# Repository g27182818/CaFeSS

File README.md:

# CaFeSS

Repository of the Cacao Fermentation Sensing System (CaFeSS) project. This is an effort by the BioMicrosystems group at Universidad de los Andes and is Authored by Gabriel Mejia and Santiago Tovar.

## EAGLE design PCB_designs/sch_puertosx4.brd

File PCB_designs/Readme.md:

### PCB Deigns

These are the Eagle files needed for the electronic components of CaFeSS

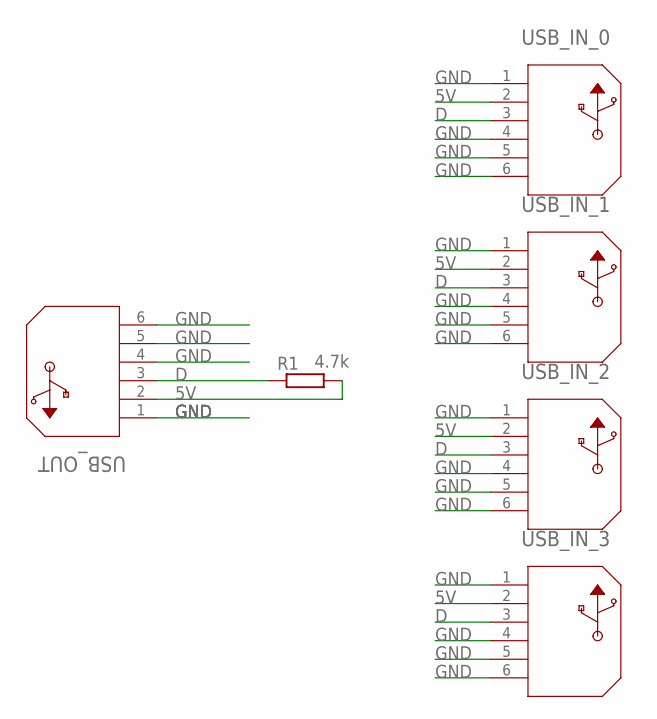
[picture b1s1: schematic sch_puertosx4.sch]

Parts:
R1: 4.7k; 0309/10
USB_IN_0, USB_IN_1, USB_IN_2, USB_IN_3: 292303-3; CONN4_292303_TEC
USB_OUT: 292303-3; CONN4_292303_TEC

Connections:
5V: R1.2, USB_IN_0.2, USB_IN_1.2, USB_IN_2.2, USB_IN_3.2, USB_OUT.2
D: R1.1, USB_IN_0.3, USB_IN_1.3, USB_IN_2.3, USB_IN_3.3, USB_OUT.3
GND: USB_IN_0.1, USB_IN_0.4, USB_IN_0.5, USB_IN_0.6, USB_IN_1.1, USB_IN_1.4, USB_IN_1.5, USB_IN_1.6, USB_IN_2.1, USB_IN_2.4, USB_IN_2.5, USB_IN_2.6, USB_IN_3.1, USB_IN_3.4, USB_IN_3.5, USB_IN_3.6, USB_OUT.1, USB_OUT.4, USB_OUT.5, USB_OUT.6

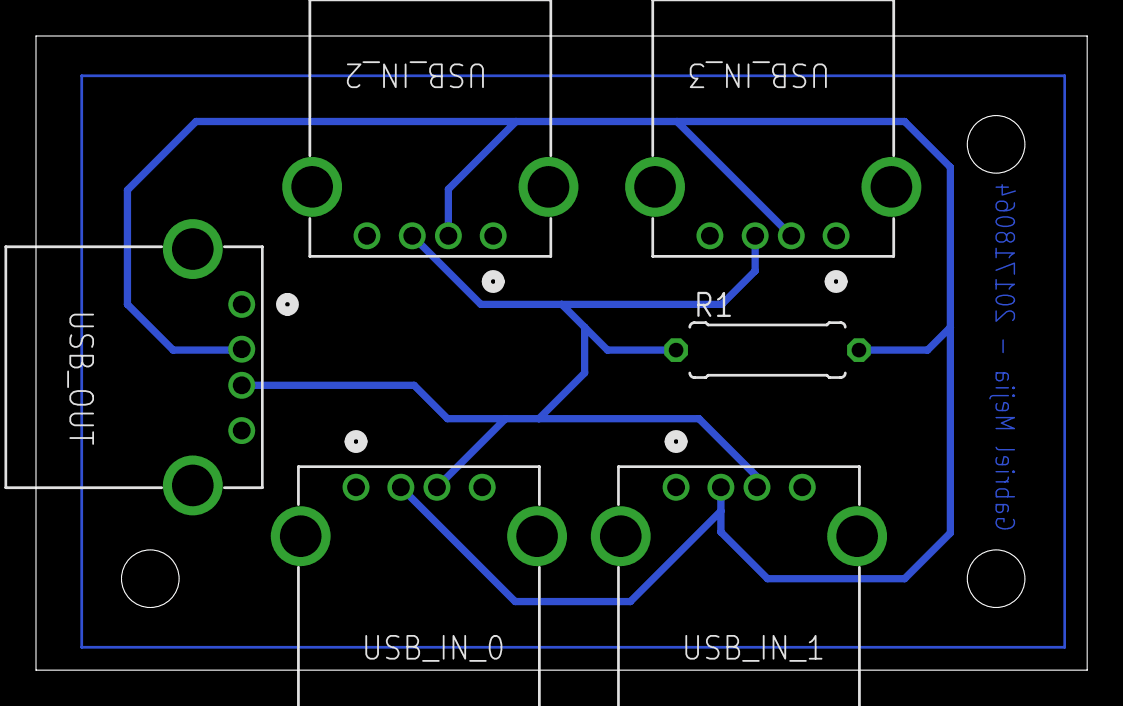
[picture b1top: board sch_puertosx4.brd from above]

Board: 2 copper layers, 58.4 x 35.2 mm, 6 parts (0 on the bottom side), 3 nets.

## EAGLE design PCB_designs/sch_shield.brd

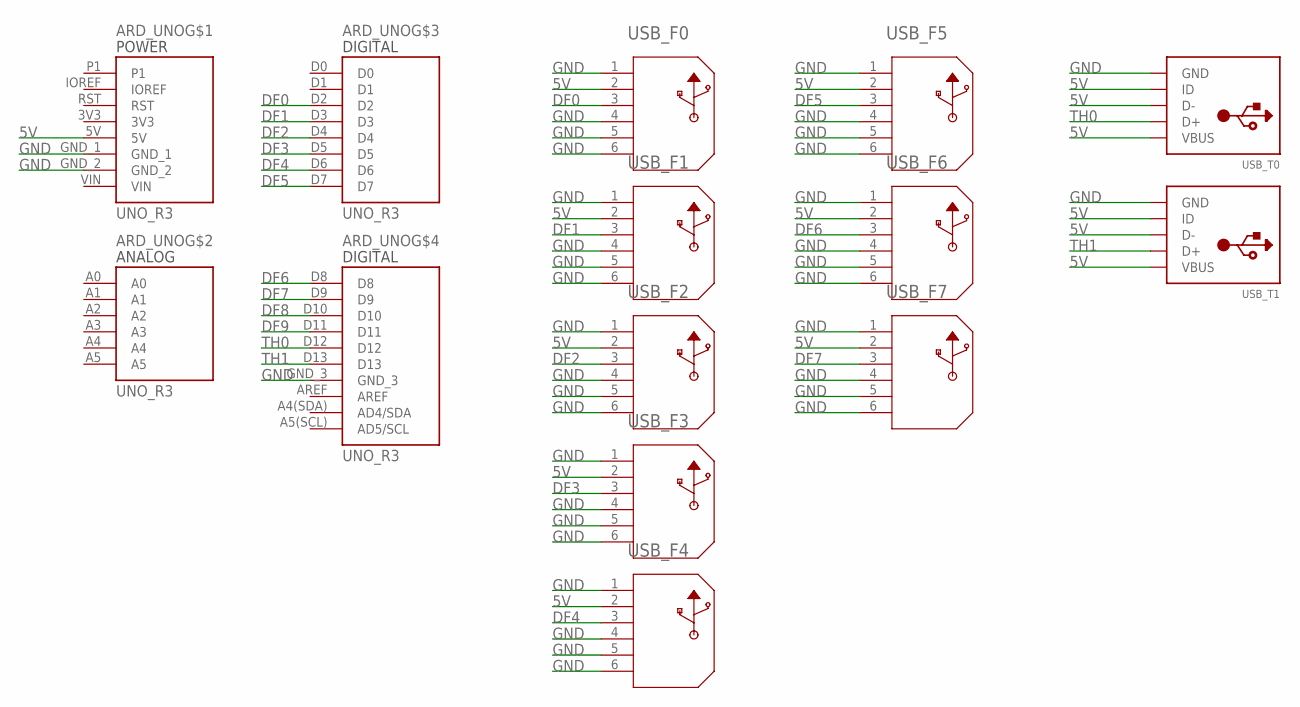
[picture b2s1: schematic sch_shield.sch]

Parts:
ARD_UNO: UNO_R3; ARDUINO_UNO_R3
USB_F0, USB_F1, USB_F2, USB_F3, USB_F4, USB_F5, USB_F6, USB_F7: 292303-3; CONN4_292303_TEC
USB_T0, USB_T1: USBTHM; USB-MINIB-THM

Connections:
3V3: ARD_UNO.3V3
5V: ARD_UNO.5V, USB_F0.2, USB_F1.2, USB_F2.2, USB_F3.2, USB_F4.2, USB_F5.2, USB_F6.2, USB_F7.2, USB_T0.D-, USB_T0.ID, USB_T0.VBUS, USB_T1.D-, USB_T1.ID, USB_T1.VBUS
DF0: ARD_UNO.D2, USB_F0.3
DF1: ARD_UNO.D3, USB_F1.3
DF2: ARD_UNO.D4, USB_F2.3
DF3: ARD_UNO.D5, USB_F3.3
DF4: ARD_UNO.D6, USB_F4.3
DF5: ARD_UNO.D7, USB_F5.3
DF6: ARD_UNO.D8, USB_F6.3
DF7: ARD_UNO.D9, USB_F7.3
DF8: ARD_UNO.D10
DF9: ARD_UNO.D11
GND: ARD_UNO.GND_1, ARD_UNO.GND_2, ARD_UNO.GND_3, USB_F0.1, USB_F0.4, USB_F0.5, USB_F0.6, USB_F1.1, USB_F1.4, USB_F1.5, USB_F1.6, USB_F2.1, USB_F2.4, USB_F2.5, USB_F2.6, USB_F3.1, USB_F3.4, USB_F3.5, USB_F3.6, USB_F4.1, USB_F4.4, USB_F4.5, USB_F4.6, USB_F5.1, USB_F5.4, USB_F5.5, USB_F5.6, USB_F6.1, USB_F6.4, USB_F6.5, USB_F6.6, USB_F7.1, USB_F7.4, USB_F7.5, USB_F7.6, USB_T0.GND, USB_T1.GND
TH0: ARD_UNO.D12, USB_T0.D+
TH1: ARD_UNO.D13, USB_T1.D+
VIN: ARD_UNO.VIN

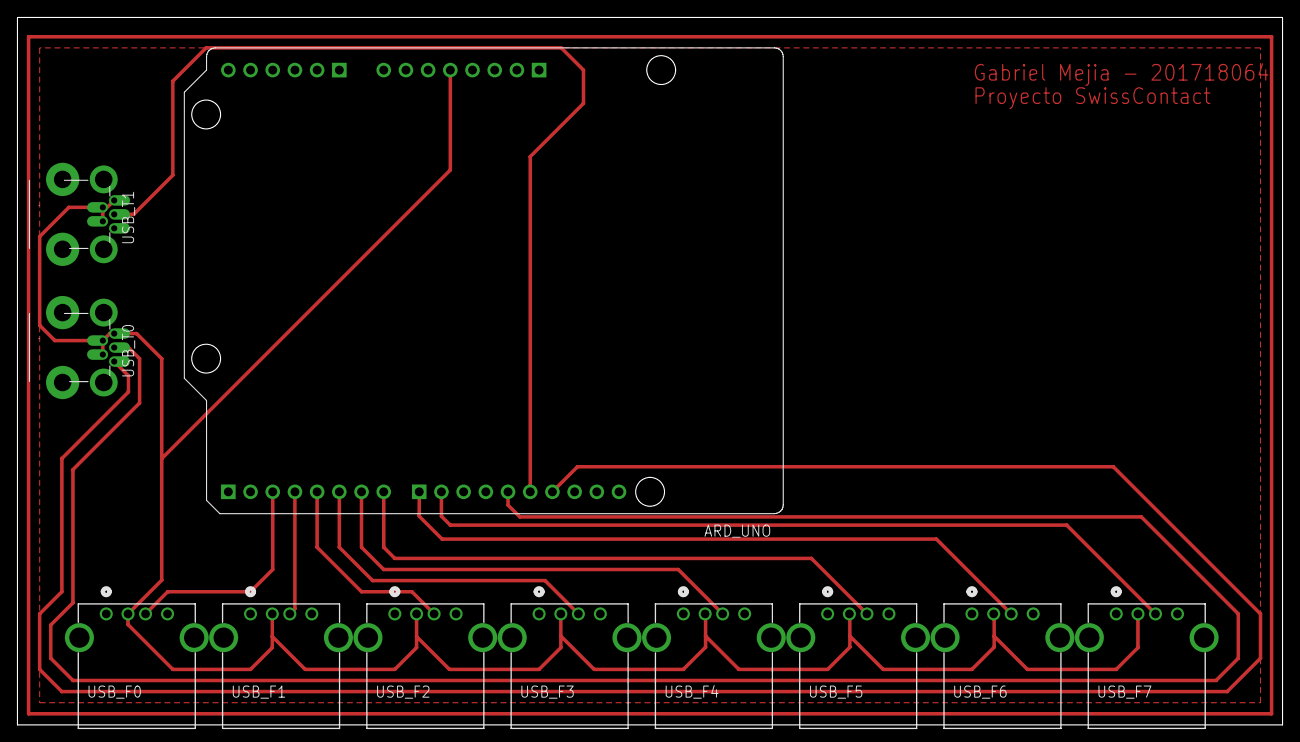
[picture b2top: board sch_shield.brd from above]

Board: 2 copper layers, 144.8 x 81.0 mm, 11 parts (0 on the bottom side), 12 nets.

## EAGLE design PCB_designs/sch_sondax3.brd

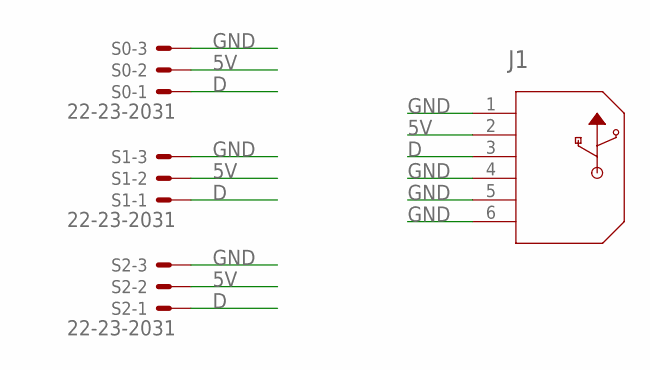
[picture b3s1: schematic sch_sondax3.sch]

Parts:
J1: 292303-3; CONN4_292303_TEC
S0, S1, S2: 22-23-2031

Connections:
5V: J1.2, S0.2, S1.2, S2.2
D: J1.3, S0.1, S1.1, S2.1
GND: J1.1, J1.4, J1.5, J1.6, S0.3, S1.3, S2.3

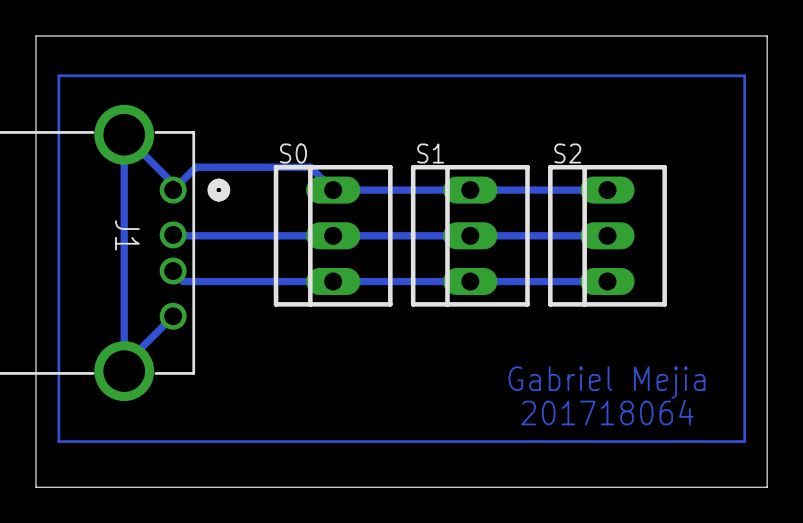
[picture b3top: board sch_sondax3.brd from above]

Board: 2 copper layers, 40.6 x 25.1 mm, 4 parts (0 on the bottom side), 3 nets.

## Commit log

2022-09-07 Test of sincronization
2022-09-07 Gitignore
2022-09-07 Modified things
2022-09-07 Modified interfaz
2022-09-07 Tasks updated
2022-09-10 Shading working in plot_fermenter_sensors
2022-09-11 Schematics
2022-09-12 Global plot working
2022-09-14 Initial version of general report
2022-09-14 High res report
2022-10-14 PysimpleGUI test
2022-10-20 Added legends and real data csv
2022-10-21 test functions file
2022-10-21 Upload from mac
2022-10-21 Final merge
2022-10-22 Added simulations with realistic data
2022-10-28 We now can produce Gif of fermenter 1
2022-10-28 Now we have utils and df filtering with date
2022-11-01 Modified to JPEG
2022-11-03 Add data images
2022-11-10 Now the report shows current 3d profile
2022-11-11 request function and test_system. Gif not working
2022-11-11 Now saves all frames and makes gif
2022-11-11 Gitignore updated
2022-11-11 No we dont have warnings in test
2022-11-11 Now gitignore finally working
2022-11-11 Gitignore working again
2022-11-11 Now tests_functions has the worst test case
2022-11-11 Minor mod
2022-11-15 Add files via upload
    Actualización de la interfaz, falta integrar parte del diccionario en detalles en las opciones, pero ya todo está funcional, cambiando las opciones cuando se cambia el tipo de grafica, con notas y vo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
2022-11-15 Add files via upload
    Ya casi
2022-11-16 Interfaz completa a falta de integración con Back
2022-11-18 First working interface with simulated data
2022-11-18 One single interface.py file
2022-11-18 Minor modifications
2022-11-18 arranges for real use
2022-11-18 added breakpoint
2022-11-18 mod to read line correctly
2022-11-18 mod of pop
2022-11-18 corrected datetime usage
2022-11-18 modify sample freq to 1 min
2022-11-24 Now we can generate dummy files
2022-11-24 Dummy files completed and uncommented

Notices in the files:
parts and their libraries:
COPYRIGHT: Copyright (C) 2016 Accelerated Designs. All rights reserved
